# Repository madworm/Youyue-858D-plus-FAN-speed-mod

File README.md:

Youyue-858D+ FAN-speed mod:
===========================

LAYOUT FILES: Proper commutation-based speed detection for the BLDC fan.

Made to be used on top of this circuit board:

MCU-adapter-board [repository](https://github.com/madworm/Youyue-858D-plus-MCU-adapter)

Firmware [repository](https://github.com/madworm/Youyue-858D-plus)

---

Safety information / disclaimer:
================================
                                                                                                                                                             
Making any modifications to this device may cause you irreversible physical harm or worse.                                                                   
You do this at your own risk.                                                                                                                                
                                                                                                                                                             
There is a significant risk of lethal electrical shock, so if you still insist of doing so, make sure to                                                     
ALWAYS UNPLUG THE MAINS CABLE before dismantling the device. Check repeatedly.                                                                               
                                                                                                                                                             
If you have an isolation transformer - do use it.

---

Before having PC-boards made, please make sure you know about your manufacturer's peculiarities!
Especially drill-sizes and their tolerances may vary too much and give you trouble.

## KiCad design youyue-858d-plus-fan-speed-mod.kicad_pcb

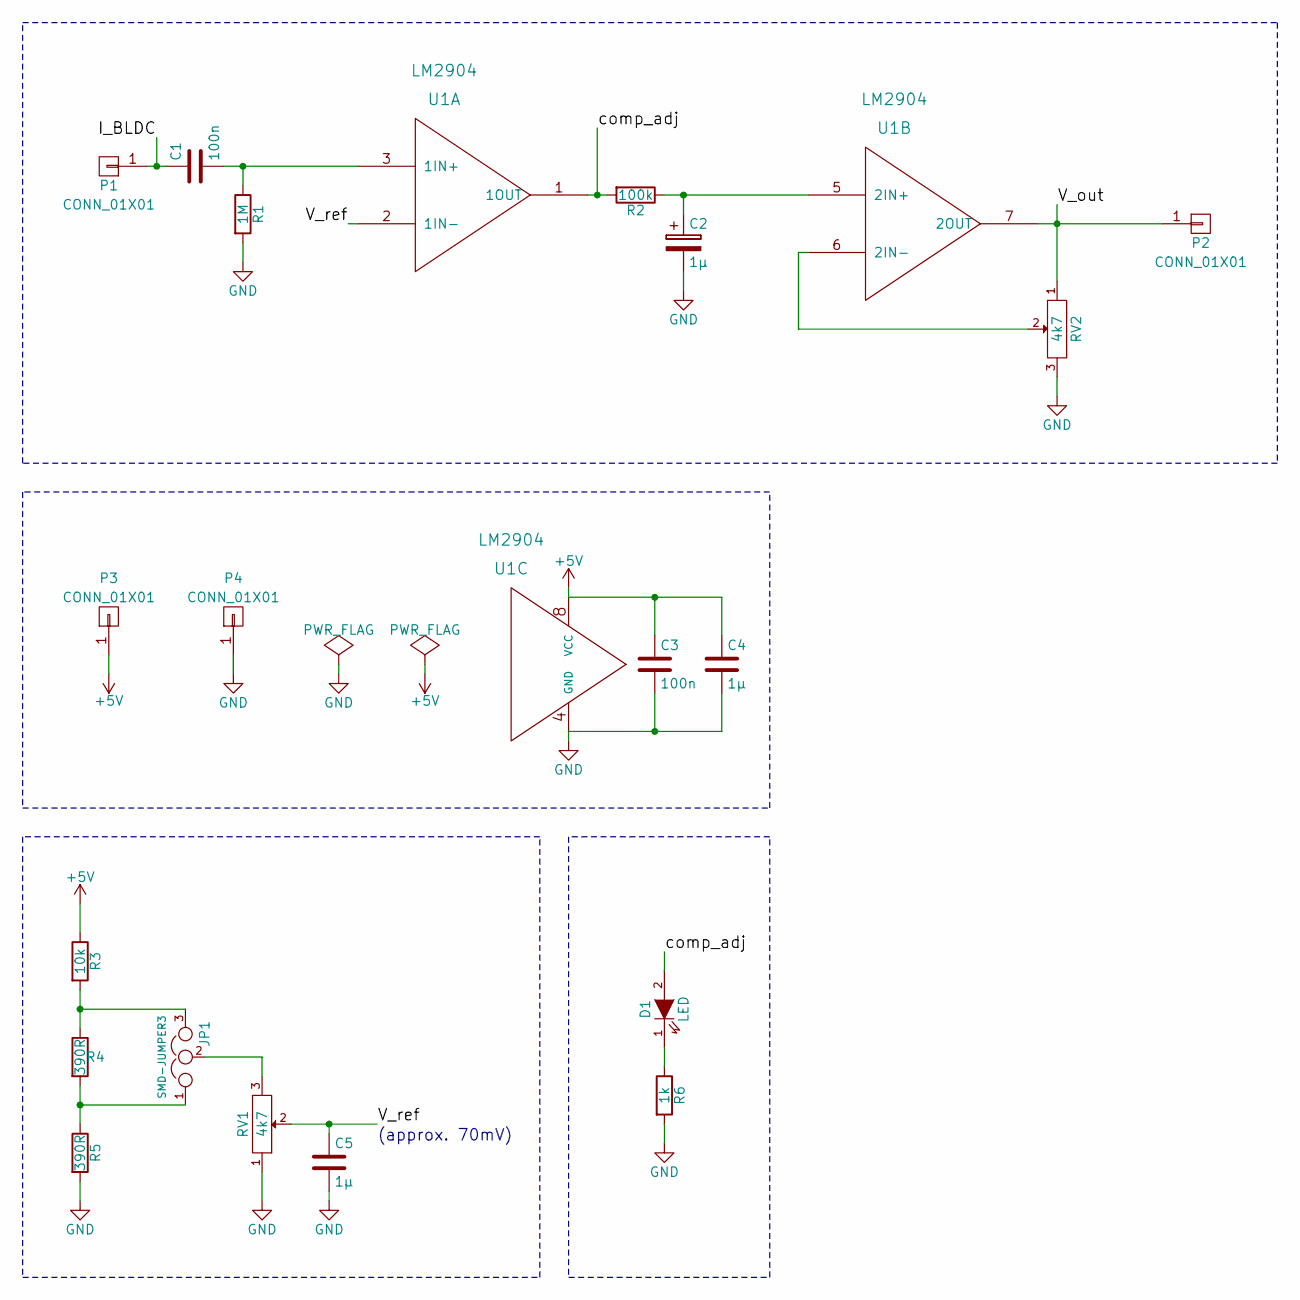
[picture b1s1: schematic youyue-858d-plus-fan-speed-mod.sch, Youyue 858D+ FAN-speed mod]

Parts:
C1, C3: 100n; C_0805_HandSoldering
C2, C4, C5: 1µ; C_0805_HandSoldering
D1: LED; LED-0805
JP1: SMD-JUMPER3; SMD-solder-bridge-3pin
P1, P2, P3, P4: CONN_01X01; SIL-1
R1: 1M; R_0805_HandSoldering
R2: 100k; R_0805_HandSoldering
R3: 10k; R_0805_HandSoldering
R4, R5: 390R; R_0805_HandSoldering
R6: 1k; R_0805_HandSoldering
RV1, RV2: 4k7; MADW__TC33X-POT
U1: LM2904; SOIC-8-N

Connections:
+5V: C3.1, C4.1, P3.1, R3.1, U1.8 (VCC)
/I_BLDC: C1.1, P1.1
/V_out: P2.1, RV2.1, U1.7 (2OUT)
/V_ref: C5.1, RV1.2, U1.2 (1IN-)
/comp_adj: D1.2 (A), R2.2, U1.1 (1OUT)
GND: C2.2, C3.2, C4.2, C5.2, P4.1, R1.2, R5.2, R6.2, RV1.1, RV2.3, U1.4 (GND)
unnamed: C1.2, R1.1, U1.3 (1IN+)
unnamed: C2.1, R2.1, U1.5 (2IN+)
unnamed: D1.1 (K), R6.1
unnamed: JP1.1, R4.2, R5.1
unnamed: JP1.2, RV1.3
unnamed: JP1.3, R3.2, R4.1
unnamed: RV2.2, U1.6 (2IN-)

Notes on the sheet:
(approx. 70mV)

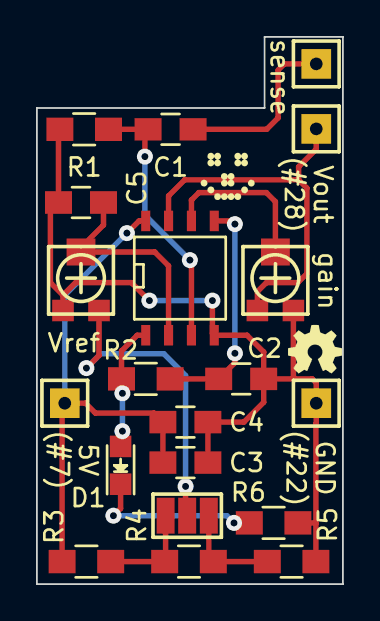
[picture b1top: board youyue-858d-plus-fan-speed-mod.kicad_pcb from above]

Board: 2 copper layers, 17.0 x 30.4 mm, 20 parts (0 on the bottom side), 13 nets.

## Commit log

2015-10-09 Moved sense-pin to free spot.
2015-10-09 Added comment.
2015-10-12 Added content to 'Docs/howto.txt'.
2015-10-15 Updated 'README.md'.
2015-10-23 Added schematic (PDF) + updated howto (2.5V).
2015-10-23 Done with Docs (I hope).
2015-10-24 Added indicator LED for easy(er) comparator adjustment (no DSO).
2015-10-24 Renamed a bunch of files.
2015-10-24 Recreated gerber files.
2015-10-24 Updated 'Docs/howto.txt' regarding the LED.
2015-10-26 Updated PNG images.
2015-10-30 Updated documentation.
2015-12-03 Fixed 'C2' in schematic: falsely marked as electrolytic.
2015-12-03 Updated image in 'README.md'.
2016-03-09 Updated 'howto.txt'.
2016-03-09 Fixed intendation.
2016-03-09 Added V1 values to 'howto.txt'.
